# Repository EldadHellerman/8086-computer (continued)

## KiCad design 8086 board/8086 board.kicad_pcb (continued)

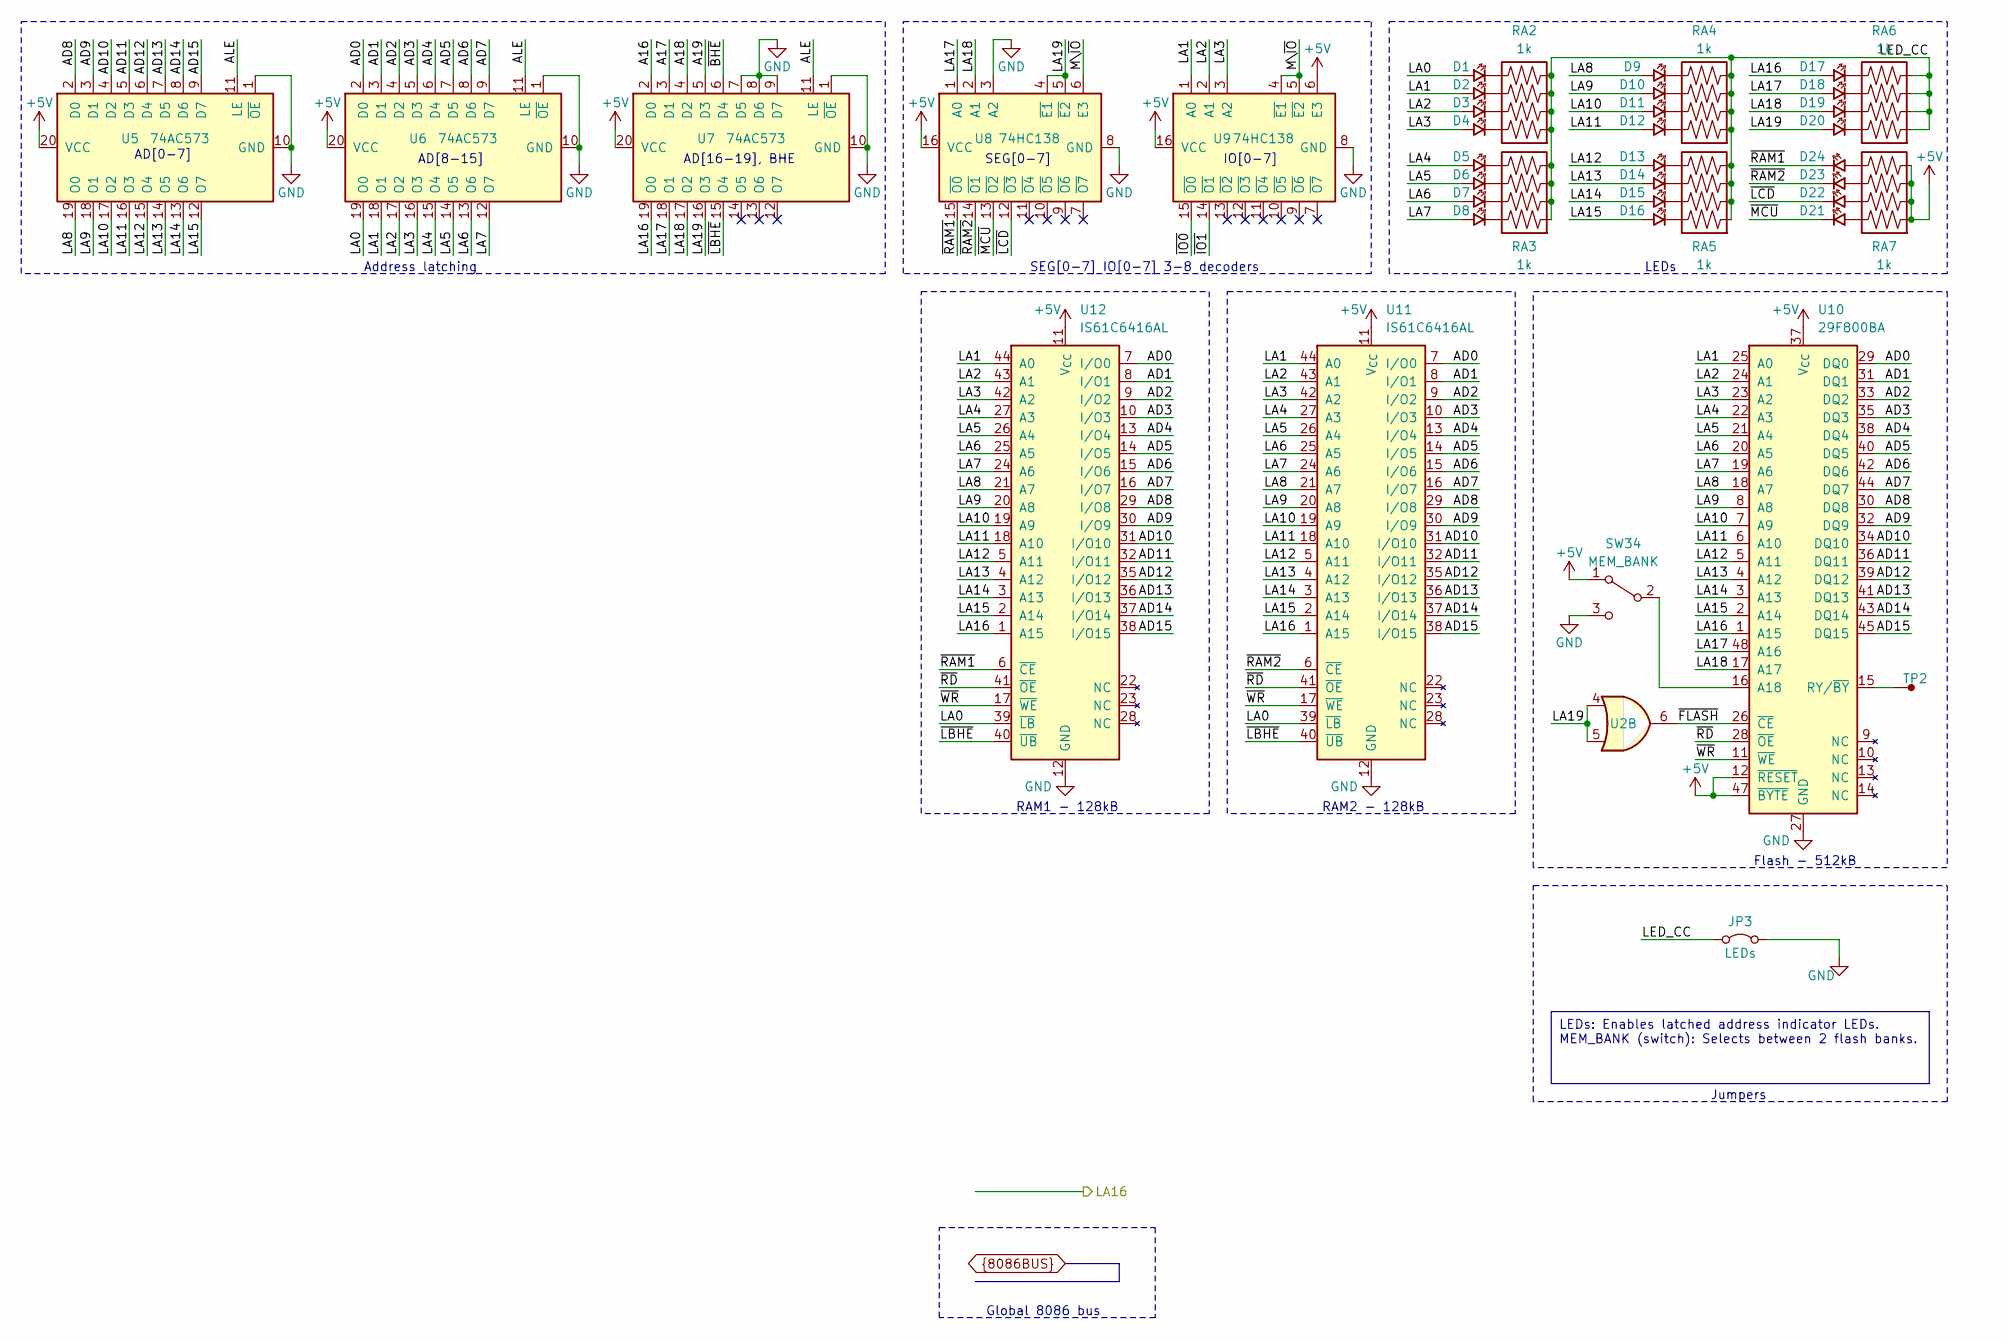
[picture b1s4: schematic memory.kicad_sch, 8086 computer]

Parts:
D1: A0; LED_0603_1608Metric_Pad1.05x0.95mm_HandSolder
D2: A1; LED_0603_1608Metric_Pad1.05x0.95mm_HandSolder
D3: A2; LED_0603_1608Metric_Pad1.05x0.95mm_HandSolder
D4: A3; LED_0603_1608Metric_Pad1.05x0.95mm_HandSolder
D5: A4; LED_0603_1608Metric_Pad1.05x0.95mm_HandSolder
D6: A5; LED_0603_1608Metric_Pad1.05x0.95mm_HandSolder
D7: A6; LED_0603_1608Metric_Pad1.05x0.95mm_HandSolder
D8: A7; LED_0603_1608Metric_Pad1.05x0.95mm_HandSolder
D9: A8; LED_0603_1608Metric_Pad1.05x0.95mm_HandSolder
D10: A9; LED_0603_1608Metric_Pad1.05x0.95mm_HandSolder
D11: A10; LED_0603_1608Metric_Pad1.05x0.95mm_HandSolder
D12: A11; LED_0603_1608Metric_Pad1.05x0.95mm_HandSolder
D13: A12; LED_0603_1608Metric_Pad1.05x0.95mm_HandSolder
D14: A13; LED_0603_1608Metric_Pad1.05x0.95mm_HandSolder
D15: A14; LED_0603_1608Metric_Pad1.05x0.95mm_HandSolder
D16: A15; LED_0603_1608Metric_Pad1.05x0.95mm_HandSolder
D17: A16; LED_0603_1608Metric_Pad1.05x0.95mm_HandSolder
D18: A17; LED_0603_1608Metric_Pad1.05x0.95mm_HandSolder
D19: A18; LED_0603_1608Metric_Pad1.05x0.95mm_HandSolder
D20: A19; LED_0603_1608Metric_Pad1.05x0.95mm_HandSolder
D21: MCU; LED_0603_1608Metric_Pad1.05x0.95mm_HandSolder
D22: LCD; LED_0603_1608Metric_Pad1.05x0.95mm_HandSolder
D23: RAM2; LED_0603_1608Metric_Pad1.05x0.95mm_HandSolder
D24: RAM1; LED_0603_1608Metric_Pad1.05x0.95mm_HandSolder
JP3: LEDs; SolderJumper-2_P1.3mm_Bridged_RoundedPad1.0x1.5mm
RA2, RA3, RA4, RA5, RA6, RA7: 1k; R_Array_Concave_4x0603
SW34: MEM_BANK; SW_SPDT_PCM12
TP2: TestPoint_Pad_1.0x1.0mm
U2: 74HC32; TSSOP-14_4.4x5mm_P0.65mm
U5, U6, U7: 74AC573; TSSOP-20_4.4x6.5mm_P0.65mm
U8, U9: 74HC138; TSSOP-16_4.4x5mm_P0.65mm
U10: 29F800BA; TSOP-I-48_18.4x12mm_P0.5mm
U11, U12: IS61C6416AL; TSOP-II-44_10.16x18.41mm_P0.8mm

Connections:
+5V: RA7.1, RA7.2, RA7.3, RA7.4, SW34.1 (A), U5.20 (VCC), U6.20 (VCC), U7.20 (VCC), U8.16 (VCC), U9.6 (E3), U9.16 (VCC), U10.12 (~RESET), U10.37 (V_{CC}), U10.47 (~BYTE), U11.11 (V_{CC}), U11.33 (V_{CC}), U12.11 (V_{CC}), U12.33 (V_{CC}); also elsewhere on the board
/IO/D/~C: D17.1 (A), U7.19 (O0), U10.1 (A15), U11.1 (A15), U12.1 (A15); also elsewhere on the board
/Memory/LA0: D1.1 (A), U6.19 (O0), U11.39 (~LB), U12.39 (~LB)
/Memory/LA1: D2.1 (A), U6.18 (O1), U9.1 (A0), U10.25 (A0), U11.44 (A0), U12.44 (A0)
/Memory/LA2: D3.1 (A), U6.17 (O2), U9.2 (A1), U10.24 (A1), U11.43 (A1), U12.43 (A1)
/Memory/LA3: D4.1 (A), U6.16 (O3), U9.3 (A2), U10.23 (A2), U11.42 (A2), U12.42 (A2)
/Memory/LA4: D5.1 (A), U6.15 (O4), U10.22 (A3), U11.27 (A3), U12.27 (A3)
/Memory/LA5: D6.1 (A), U6.14 (O5), U10.21 (A4), U11.26 (A4), U12.26 (A4)
/Memory/LA6: D7.1 (A), U6.13 (O6), U10.20 (A5), U11.25 (A5), U12.25 (A5)
/Memory/LA7: D8.1 (A), U6.12 (O7), U10.19 (A6), U11.24 (A6), U12.24 (A6)
/Memory/LA8: D9.1 (A), U5.19 (O0), U10.18 (A7), U11.21 (A7), U12.21 (A7)
/Memory/LA9: D10.1 (A), U5.18 (O1), U10.8 (A8), U11.20 (A8), U12.20 (A8)
/Memory/LA10: D11.1 (A), U5.17 (O2), U10.7 (A9), U11.19 (A9), U12.19 (A9)
/Memory/LA11: D12.1 (A), U5.16 (O3), U10.6 (A10), U11.18 (A10), U12.18 (A10)
/Memory/LA12: D13.1 (A), U5.15 (O4), U10.5 (A11), U11.5 (A11), U12.5 (A11)
/Memory/LA13: D14.1 (A), U5.14 (O5), U10.4 (A12), U11.4 (A12), U12.4 (A12)
/Memory/LA14: D15.1 (A), U5.13 (O6), U10.3 (A13), U11.3 (A13), U12.3 (A13)
/Memory/LA15: D16.1 (A), U5.12 (O7), U10.2 (A14), U11.2 (A14), U12.2 (A14)
/Memory/LA17: D18.1 (A), U7.18 (O1), U8.1 (A0), U10.48 (A16)
/Memory/LA18: D19.1 (A), U7.17 (O2), U8.2 (A1), U10.17 (A17)
/Memory/LA19: D20.1 (A), U2.4, U2.5, U7.16 (O3), U8.4 (~E1), U8.5 (~E2)
/Memory/LED_CC: JP3.1 (A), RA2.1, RA2.2, RA2.3, RA2.4, RA3.1, RA3.2, RA3.3, RA3.4, RA4.1, RA4.2, RA4.3, RA4.4, RA5.1, RA5.2, RA5.3, RA5.4, RA6.1, RA6.2, RA6.3, RA6.4
/Memory/~FLASH: U2.6, U10.26 (~CE)
/Memory/~LBHE: U7.15 (O4), U11.40 (~UB), U12.40 (~UB)
/Memory/~RAM1: D24.2 (K), U8.15 (~O0), U12.6 (~CE)
/Memory/~RAM2: D23.2 (K), U8.14 (~O1), U11.6 (~CE)
A16: U7.2 (D0); also elsewhere on the board
A17: U7.3 (D1); also elsewhere on the board
A18: U7.4 (D2); also elsewhere on the board
A19: U7.5 (D3); also elsewhere on the board
AD0: U6.2 (D0), U10.29 (DQ0), U11.7 (I/O0), U12.7 (I/O0); also elsewhere on the board
AD1: U6.3 (D1), U10.31 (DQ1), U11.8 (I/O1), U12.8 (I/O1); also elsewhere on the board
AD2: U6.4 (D2), U10.33 (DQ2), U11.9 (I/O2), U12.9 (I/O2); also elsewhere on the board
AD3: U6.5 (D3), U10.35 (DQ3), U11.10 (I/O3), U12.10 (I/O3); also elsewhere on the board
AD4: U6.6 (D4), U10.38 (DQ4), U11.13 (I/O4), U12.13 (I/O4); also elsewhere on the board
AD5: U6.7 (D5), U10.40 (DQ5), U11.14 (I/O5), U12.14 (I/O5); also elsewhere on the board
AD6: U6.8 (D6), U10.42 (DQ6), U11.15 (I/O6), U12.15 (I/O6); also elsewhere on the board
AD7: U6.9 (D7), U10.44 (DQ7), U11.16 (I/O7), U12.16 (I/O7); also elsewhere on the board
AD8: U5.2 (D0), U10.30 (DQ8), U11.29 (I/O8), U12.29 (I/O8); also elsewhere on the board
AD9: U5.3 (D1), U10.32 (DQ9), U11.30 (I/O9), U12.30 (I/O9); also elsewhere on the board
AD10: U5.4 (D2), U10.34 (DQ10), U11.31 (I/O10), U12.31 (I/O10); also elsewhere on the board
AD11: U5.5 (D3), U10.36 (DQ11), U11.32 (I/O11), U12.32 (I/O11); also elsewhere on the board
AD12: U5.6 (D4), U10.39 (DQ12), U11.35 (I/O12), U12.35 (I/O12); also elsewhere on the board
AD13: U5.7 (D5), U10.41 (DQ13), U11.36 (I/O13), U12.36 (I/O13); also elsewhere on the board
AD14: U5.8 (D6), U10.43 (DQ14), U11.37 (I/O14), U12.37 (I/O14); also elsewhere on the board
AD15: U5.9 (D7), U10.45 (DQ15), U11.38 (I/O15), U12.38 (I/O15); also elsewhere on the board
ALE: U5.11 (LE), U6.11 (LE), U7.11 (LE); also elsewhere on the board
GND: JP3.2 (B), SW34.3 (C), U5.1 (~OE), U5.10 (GND), U6.1 (~OE), U6.10 (GND), U7.1 (~OE), U7.7 (D5), U7.8 (D6), U7.9 (D7), U7.10 (GND), U8.3 (A2), U8.8 (GND), U9.8 (GND), U10.27 (GND), U10.46 (GND), U11.12 (GND), U11.34 (GND), U12.12 (GND), U12.34 (GND); also elsewhere on the board
M\~IO: U8.6 (E3), U9.4 (~E1), U9.5 (~E2); also elsewhere on the board
unnamed: D1.2 (K), RA2.5
unnamed: D2.2 (K), RA2.6
unnamed: D3.2 (K), RA2.7
unnamed: D4.2 (K), RA2.8
unnamed: D5.2 (K), RA3.5
unnamed: D6.2 (K), RA3.6
unnamed: D7.2 (K), RA3.7
unnamed: D8.2 (K), RA3.8
unnamed: D9.2 (K), RA4.5
unnamed: D10.2 (K), RA4.6
unnamed: D11.2 (K), RA4.7
unnamed: D12.2 (K), RA4.8
unnamed: D13.2 (K), RA5.5
unnamed: D14.2 (K), RA5.6
unnamed: D15.2 (K), RA5.7
unnamed: D16.2 (K), RA5.8
unnamed: D17.2 (K), RA6.5
unnamed: D18.2 (K), RA6.6
unnamed: D19.2 (K), RA6.7
unnamed: D20.2 (K), RA6.8
unnamed: D21.1 (A), RA7.8
unnamed: D22.1 (A), RA7.7
unnamed: D23.1 (A), RA7.6
unnamed: D24.1 (A), RA7.5
unnamed: SW34.2 (B), U10.16 (A18)
unnamed: TP2.1, U10.15 (RY/~BY)
~BHE: U7.6 (D4); also elsewhere on the board
~IO0: U9.15 (~O0); also elsewhere on the board
~IO1: U9.14 (~O1); also elsewhere on the board
~LCD: D22.2 (K), U8.12 (~O3); also elsewhere on the board
~MCU: D21.2 (K), U8.13 (~O2); also elsewhere on the board
~RD: U10.28 (~OE), U11.41 (~OE), U12.41 (~OE); also elsewhere on the board
~WR: U10.11 (~WE), U11.17 (~WE), U12.17 (~WE); also elsewhere on the board

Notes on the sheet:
LEDs: Enables latched address indicator LEDs. MEM_BANK (switch): Selects between 2 flash banks.
IO[0-7]
AD[16-19], BHE
SEG[0-7] IO[0-7] 3-8 decoders
RAM1 - 128kB
Address latching
AD[0-7]
LEDs
AD[8-15]
SEG[0-7]
Jumpers
RAM2 - 128kB
Flash - 512kB
Global 8086 bus

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
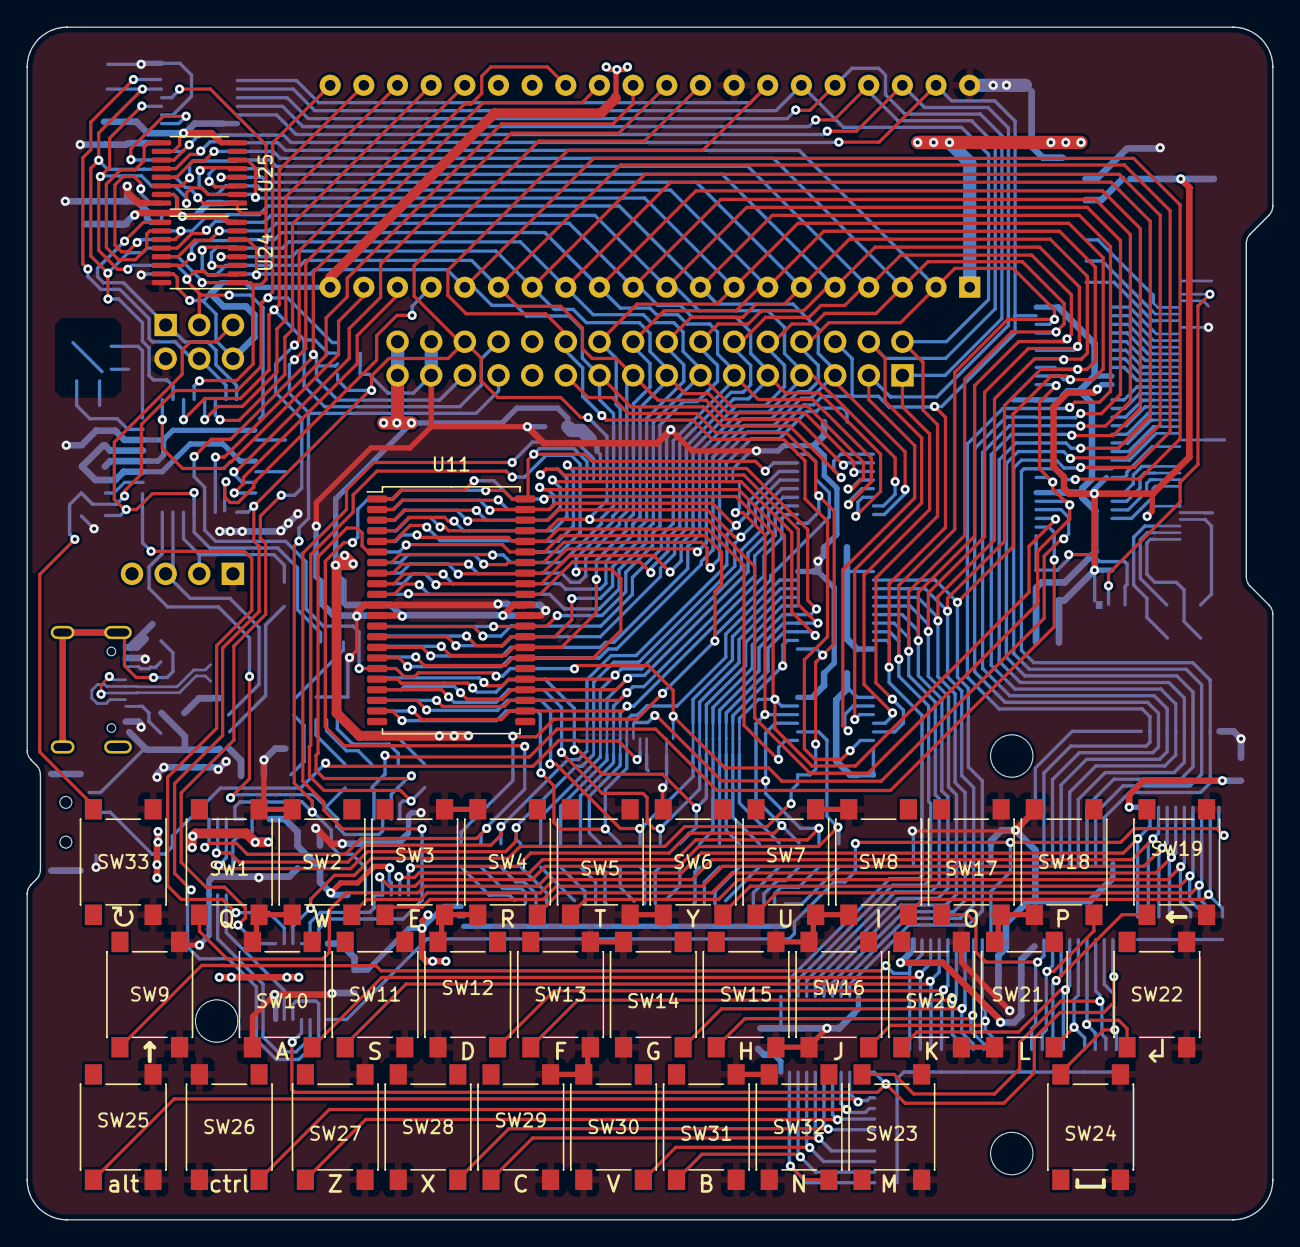
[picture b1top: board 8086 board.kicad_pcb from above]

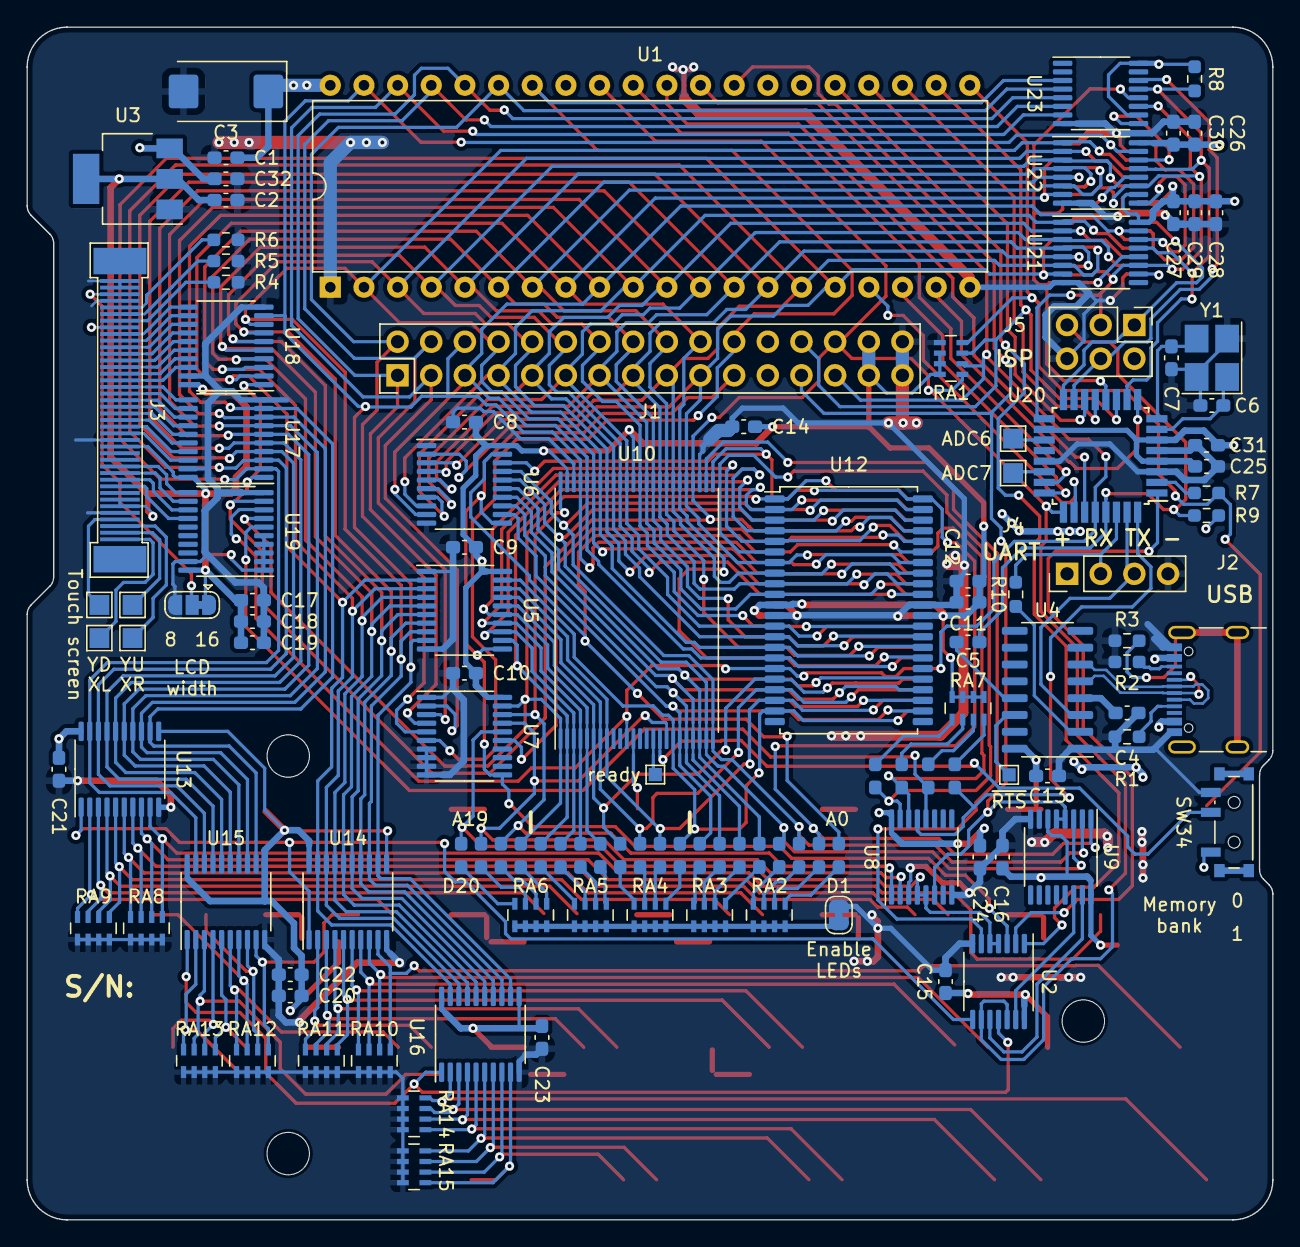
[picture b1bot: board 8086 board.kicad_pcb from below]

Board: 2 copper layers, 94.0 x 90.0 mm, 159 parts (123 on the bottom side), 181 nets.

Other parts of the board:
C4: 1uF; C_0603_1608Metric_Pad1.08x0.95mm_HandSolder
TP3: XL; TestPoint_Pad_1.5x1.5mm
TP4: YU; TestPoint_Pad_1.5x1.5mm
TP5: XR; TestPoint_Pad_1.5x1.5mm
TP6: YD; TestPoint_Pad_1.5x1.5mm
TP7: ADC6; TestPoint_Pad_1.5x1.5mm
TP8: ADC7; TestPoint_Pad_1.5x1.5mm
U4: CH340C; SOIC-16_3.9x9.9mm_P1.27mm

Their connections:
+5V: U4.16 (VCC); also elsewhere on the board
/Microcontroller/DN: U4.6 (UD-); also elsewhere on the board
/Microcontroller/DP: U4.5 (UD+); also elsewhere on the board
/Microcontroller/RX: U4.3 (RXD); also elsewhere on the board
GND: C4.1, U4.1 (GND); also elsewhere on the board
unnamed 155: U4.2 (TXD); also elsewhere on the board
unnamed: C4.2, U4.4 (V3)
unnamed 157: U4.13 (~DTR); also elsewhere on the board

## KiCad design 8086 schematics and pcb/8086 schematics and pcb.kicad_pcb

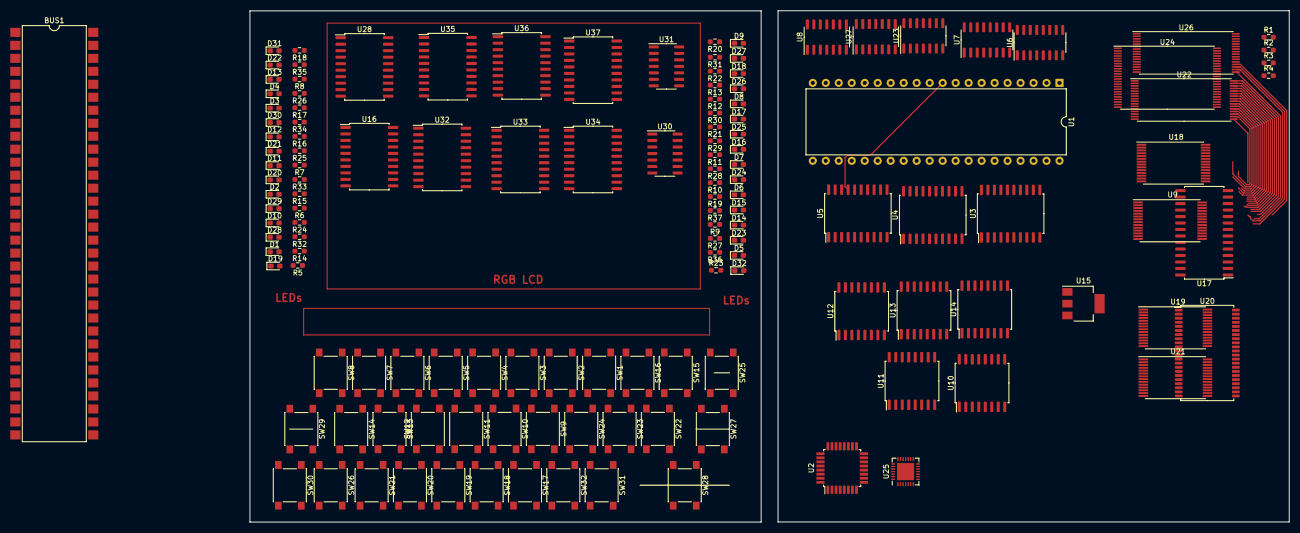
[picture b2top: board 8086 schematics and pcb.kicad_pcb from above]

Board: 2 copper layers, 203.3 x 100.0 mm, 138 parts (0 on the bottom side), 198 nets.

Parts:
BUS1: 8086 BUS; SMDIP-64_W15.24mm
D1, D2, D3, D4, D5, D6, D7, D8, D9, D10, D11, D12, D13, D14, D15, D16, D17, D18, D19, D20, D21, D22, D23, D24, D25, D26, D27, D28, D29, D30, D31, D32: LED_Filled; LED_0603_1608Metric_Pad1.05x0.95mm_HandSolder
R1, R2, R3, R4: 10K; R_0603_1608Metric_Pad0.98x0.95mm_HandSolder
R5, R6, R7, R8, R9, R10, R11, R12, R13, R14, R15, R16, R17, R18, R19, R20, R21, R22, R23, R24, R25, R26, R27, R28, R29, R30, R31, R32, R33, R34, R35, R36, R37: R_US; R_0603_1608Metric_Pad0.98x0.95mm_HandSolder
SW1, SW2, SW3, SW4, SW5, SW6, SW7, SW8, SW9, SW10, SW11, SW12, SW13, SW14, SW15, SW16, SW17, SW18, SW19, SW20, SW21, SW22, SW23, SW24, SW25, SW26, SW27, SW28, SW29, SW30, SW31, SW32: SW_Push; SW_Push_1P1T_NO_6x6mm_H9.5mm
U1: P8086-2; DIP-40_W15.24mm
U2: ATmega328P-A; TQFP-32_7x7mm_P0.8mm
U3, U4, U5: 74HC373; SOIC-20W_7.5x12.8mm_P1.27mm
U6, U7: 74LS138; SOIC-16_3.9x9.9mm_P1.27mm
U8, U30: 74AC00; SOIC-14_3.9x8.7mm_P1.27mm
U9, U18, U19, U21: IS61C256AH; TSOP-I-28_11.8x8mm_P0.55mm
U10, U11, U12: 74HC595; SOIC-16W_7.5x10.3mm_P1.27mm
U13, U14: 74HC165; SOIC-16W_7.5x10.3mm_P1.27mm
U15: AMS1117-3.3; SOT-223-3_TabPin2
U16, U28, U32, U33, U34, U35, U36, U37: 74AC373; SOIC-20W_7.5x12.8mm_P1.27mm
U17: CXK58257AM; SOIC-28W_7.5x17.9mm_P1.27mm
U20: IS61C3216; TSOP-II-44_10.16x18.41mm_P0.8mm
U22, U26: AM29F002; TSOP-I-32_18.4x8mm_P0.5mm
U23: 74HC14; SOIC-14_3.9x8.7mm_P1.27mm
U24: 28F400; TSOP-I-48_18.4x12mm_P0.5mm
U25: CP2102N-Axx-xQFN28; QFN-28-1EP_5x5mm_P0.5mm_EP3.35x3.35mm
U27, U31: 74HC02; SOIC-14_3.9x8.7mm_P1.27mm

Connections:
+3.3V: BUS1.43 (3V3), BUS1.44 (3V3), U15.2 (VO)
+5V: BUS1.41 (5V), BUS1.42 (5V), R1.1, R2.1, R3.1, R4.1, SW1.1, SW2.1, SW3.1, SW4.1, SW5.1, SW6.1, SW7.1, SW8.1, SW9.1, SW10.1, SW11.1, SW12.1, SW13.1, SW14.1, SW15.1, SW16.1, SW17.1, SW18.1, SW19.1, SW20.1, SW21.1, SW22.1, SW23.1, SW24.1, SW25.1, SW26.1, SW27.1, SW28.1, SW29.1, SW30.1, SW31.1, SW32.1, U1.33 (NM/~MX), U1.40 (V_{CC}), U2.4 (VCC), U2.6 (VCC), U2.18 (AVCC), U3.20 (VCC), U4.20 (VCC), U5.20 (VCC), U6.6 (E3), U6.16 (VCC), U7.16 (VCC), U8.14 (V_{CC}), U9.28 (V_{CC}), U10.16 (VCC), U11.16 (VCC), U12.16 (VCC), U13.16 (V_{CC}), U14.16 (V_{CC}), U15.3 (VI), U16.20 (VCC), U17.28 (V_{CC}), U18.28 (V_{CC}), U19.28 (V_{CC}), U20.11 (V_{CC}), U20.33 (V_{CC}), U21.28 (V_{CC}), U22.8 (V_{CC}), U22.9 (~RESET), U23.14 (V_{CC}), U24.12 (~RP), U24.13 (V_{PP}), U24.14 (~WP), U24.37 (V_{CC}), U24.47 (~BYTE), U26.8 (V_{CC}), U26.9 (~RESET), U27.14 (V_{CC}), U28.20 (VCC), U30.14 (V_{CC}), U31.14 (V_{CC}), U32.20 (VCC), U33.20 (VCC), U34.20 (VCC), U35.20 (VCC), U36.20 (VCC), U37.20 (VCC)
/8086 Module - 1/ALE: U3.11 (LE), U4.11 (LE), U5.11 (LE), U23.12
/8086 Module - 1/CPUALE: U1.25 (ALE), U27.2
/8086 Module - 1/LA0: U5.2 (O0), U20.39 (~LB), U23.1
/8086 Module - 1/LA1: U5.5 (O1), U6.1 (A0), U9.10 (A0), U17.10 (A0), U18.10 (A0), U19.10 (A0), U20.44 (A0), U21.10 (A0), U22.20 (A0), U24.25 (A0), U26.20 (A0)
/8086 Module - 1/LA2: U5.6 (O2), U6.2 (A1), U9.9 (A1), U17.9 (A1), U18.9 (A1), U19.9 (A1), U20.43 (A1), U21.9 (A1), U22.19 (A1), U24.24 (A1), U26.19 (A1)
/8086 Module - 1/LA3: U5.9 (O3), U6.3 (A2), U9.8 (A2), U17.8 (A2), U18.8 (A2), U19.8 (A2), U20.42 (A2), U21.8 (A2), U22.18 (A2), U24.23 (A2), U26.18 (A2)
/8086 Module - 1/LA4: U5.12 (O4), U9.7 (A3), U17.7 (A3), U18.7 (A3), U19.7 (A3), U20.27 (A3), U21.7 (A3), U22.17 (A3), U24.22 (A3), U26.17 (A3)
/8086 Module - 1/LA5: U5.15 (O5), U9.6 (A4), U17.6 (A4), U18.6 (A4), U19.6 (A4), U20.26 (A4), U21.6 (A4), U22.16 (A4), U24.21 (A4), U26.16 (A4)
/8086 Module - 1/LA6: U5.16 (O6), U9.5 (A5), U17.5 (A5), U18.5 (A5), U19.5 (A5), U20.25 (A5), U21.5 (A5), U22.15 (A5), U24.20 (A5), U26.15 (A5)
/8086 Module - 1/LA7: U5.19 (O7), U9.4 (A6), U17.4 (A6), U18.4 (A6), U19.4 (A6), U20.24 (A6), U21.4 (A6), U22.14 (A6), U24.19 (A6), U26.14 (A6)
/8086 Module - 1/LA8: U3.2 (O0), U9.3 (A7), U17.3 (A7), U18.3 (A7), U19.3 (A7), U20.21 (A7), U21.3 (A7), U22.13 (A7), U24.18 (A7), U26.13 (A7)
/8086 Module - 1/LA9: U3.5 (O1), U9.25 (A8), U17.25 (A8), U18.25 (A8), U19.25 (A8), U20.20 (A8), U21.25 (A8), U22.3 (A8), U24.8 (A8), U26.3 (A8)
/8086 Module - 1/LA10: U3.6 (O2), U9.24 (A9), U17.24 (A9), U18.24 (A9), U19.24 (A9), U20.19 (A9), U21.24 (A9), U22.2 (A9), U24.7 (A9), U26.2 (A9)
/8086 Module - 1/LA11: U3.9 (O3), U9.21 (A10), U17.21 (A10), U18.21 (A10), U19.21 (A10), U20.18 (A10), U21.21 (A10), U22.31 (A10), U24.6 (A10), U26.31 (A10)
/8086 Module - 1/LA12: U3.12 (O4), U9.23 (A11), U17.23 (A11), U18.23 (A11), U19.23 (A11), U20.5 (A11), U21.23 (A11), U22.1 (A11), U24.5 (A11), U26.1 (A11)
/8086 Module - 1/LA13: U3.15 (O5), U9.2 (A12), U17.2 (A12), U18.2 (A12), U19.2 (A12), U20.4 (A12), U21.2 (A12), U22.12 (A12), U24.4 (A12), U26.12 (A12)
/8086 Module - 1/LA14: U3.16 (O6), U9.26 (A13), U17.26 (A13), U18.26 (A13), U19.26 (A13), U20.3 (A13), U21.26 (A13), U22.4 (A13), U24.3 (A13), U26.4 (A13)
/8086 Module - 1/LA15: U3.19 (O7), U9.1 (A14), U17.1 (A14), U18.1 (A14), U19.1 (A14), U20.2 (A14), U21.1 (A14), U22.5 (A14), U24.2 (A14), U26.5 (A14)
/8086 Module - 1/LA16: U4.2 (O0), U7.1 (A0), U22.11 (A15), U24.1 (A15), U26.11 (A15)
/8086 Module - 1/LA17: U4.5 (O1), U7.2 (A1), U22.10 (A16), U24.48 (A16), U26.10 (A16)
/8086 Module - 1/LA18: U4.6 (O2), U7.3 (A2), U22.6 (A17), U24.17 (A17), U26.6 (A17)
/8086 Module - 1/LA19: U4.9 (O3), U7.4 (~E1), U7.5 (~E2), U23.3
/8086 Module - 1/LBHE: U8.5, U8.13, U23.10
/8086 Module - 1/M/~IO: U1.28 (M/~IO), U6.4 (~E1), U6.5 (~E2), U7.6 (E3)
/8086 Module - 1/SEG0: U8.2, U8.4, U23.8
/8086 Module - 1/~LA0: U8.1, U8.9, U23.2
/8086 Module - 1/~LA19: U23.4, U24.26 (~CE)
/8086 Module - 1/~LBHE: U4.12 (O4), U20.40 (~UB), U23.11
/8086 Module - 1/~SEG0: U7.15 (~O0), U23.9
/8086 Module - 1/~SEG1: U7.14 (~O1), U20.6 (~CE), U23.5
/8086 Module - 2/~MEM1H: U8.11, U21.20 (~CE), U26.30 (~CE)
/8086 Module - 2/~MEM1L: U8.8, U19.20 (~CE), U22.30 (~CE)
/8086 Module - 2/~SEG0H: U8.6, U18.20 (~CE)
/8086 Module - 2/~SEG0L: U8.3, U9.20 (~CE), U17.20 (~CE)
/8086 Module - 2/~WRP: U22.7 (~WE), U24.11 (~WE), U26.7 (~WE)
/IO Module/WR0: U28.11 (LE), U31.10, U35.11 (LE)
/IO Module/WR1: U31.13, U36.11 (LE), U37.11 (LE)
/IO Module/~RD0: U16.1 (~OE), U30.3, U32.1 (~OE)
/IO Module/~RD1: U30.6, U33.1 (~OE), U34.1 (~OE)
/Microcontroller Module/REG_OE: U2.23 (PC0), U10.13 (~OE), U11.13 (~OE), U12.13 (~OE)
/Microcontroller Module/REG_RCLK: U2.14 (PB2), U10.12 (RCLK), U11.12 (RCLK), U12.12 (RCLK)
/Microcontroller Module/REG_SHLD: U2.24 (PC1), U13.1 (SH/~LD), U14.1 (SH/~LD)
/Microcontroller Module/SPI_MISO: U2.16 (PB4), U14.9 (QH)
/Microcontroller Module/SPI_MOSI: U2.15 (PB3), U10.14 (SER)
/Microcontroller Module/SPI_SCK: U2.17 (PB5), U10.11 (SRCLK), U11.11 (SRCLK), U12.11 (SRCLK)
A16: BUS1.17 (A16), U1.38 (A16), U4.3 (D0), U12.15 (QA)
A17: BUS1.18 (A17), U1.37 (A17), U4.4 (D1), U12.1 (QB)
A18: BUS1.19 (A18), U1.36 (A18), U4.7 (D2), U12.2 (QC)
A19: BUS1.20 (A19), U1.35 (A19), U4.8 (D3), U12.3 (QD)
AD0: BUS1.1 (AD0), U1.16 (AD0), U5.3 (D0), U9.11 (I/O0), U10.15 (QA), U13.11 (A), U16.2 (O0), U17.11 (I/O0), U19.11 (I/O0), U20.7 (I/O0), U22.21 (DQ0), U24.29 (DQ0), U28.3 (D0), U33.2 (O0), U36.3 (D0)
AD1: BUS1.2 (AD1), BUS1.3 (AD2), U1.15 (AD1), U5.4 (D1), U9.12 (I/O1), U10.1 (QB), U13.12 (B), U16.5 (O1), U17.12 (I/O1), U19.12 (I/O1), U20.8 (I/O1), U22.22 (DQ1), U24.31 (DQ1), U28.4 (D1), U33.5 (O1), U36.4 (D1)
AD2: U1.14 (AD2), U5.7 (D2), U9.13 (I/O2), U10.2 (QC), U13.13 (C), U16.6 (O2), U17.13 (I/O2), U19.13 (I/O2), U20.9 (I/O2), U22.23 (DQ2), U24.33 (DQ2), U28.7 (D2), U33.6 (O2), U36.7 (D2)
AD3: BUS1.4 (AD3), U1.13 (AD3), U5.8 (D3), U9.15 (I/O3), U10.3 (QD), U13.14 (D), U16.9 (O3), U17.15 (I/O3), U19.15 (I/O3), U20.10 (I/O3), U22.25 (DQ3), U24.35 (DQ3), U28.8 (D3), U33.9 (O3), U36.8 (D3)
AD4: BUS1.5 (AD4), U1.12 (AD4), U5.13 (D4), U9.16 (I/O4), U10.4 (QE), U13.3 (E), U16.12 (O4), U17.16 (I/O4), U19.16 (I/O4), U20.13 (I/O4), U22.26 (DQ4), U24.38 (DQ4), U28.13 (D4), U33.12 (O4), U36.13 (D4)
AD5: BUS1.6 (AD5), U1.11 (AD5), U5.14 (D5), U9.17 (I/O5), U10.5 (QF), U13.4 (F), U16.15 (O5), U17.17 (I/O5), U19.17 (I/O5), U20.14 (I/O5), U22.27 (DQ5), U24.40 (DQ5), U28.14 (D5), U33.15 (O5), U36.14 (D5)
AD6: BUS1.7 (AD6), U1.10 (AD6), U5.17 (D6), U9.18 (I/O6), U10.6 (QG), U13.5 (G), U16.16 (O6), U17.18 (I/O6), U19.18 (I/O6), U20.15 (I/O6), U22.28 (DQ6), U24.42 (DQ6), U28.17 (D6), U33.16 (O6), U36.17 (D6)
AD7: BUS1.8 (AD7), U1.9 (AD7), U5.18 (D7), U9.19 (I/O7), U10.7 (QH), U13.6 (H), U16.19 (O7), U17.19 (I/O7), U19.19 (I/O7), U20.16 (I/O7), U22.29 (DQ7), U24.44 (DQ7), U28.18 (D7), U33.19 (O7), U36.18 (D7)
AD8: BUS1.9 (AD8), U1.8 (AD8), U3.3 (D0), U11.15 (QA), U14.11 (A), U18.11 (I/O0), U20.29 (I/O8), U21.11 (I/O0), U24.30 (DQ8), U26.21 (DQ0), U32.2 (O0), U34.2 (O0), U35.3 (D0), U37.3 (D0)
AD9: BUS1.10 (AD9), U1.7 (AD9), U3.4 (D1), U11.1 (QB), U14.12 (B), U18.12 (I/O1), U20.30 (I/O9), U21.12 (I/O1), U24.32 (DQ9), U26.22 (DQ1), U32.5 (O1), U34.5 (O1), U35.4 (D1), U37.4 (D1)
AD10: BUS1.11 (AD10), U1.6 (AD10), U3.7 (D2), U11.2 (QC), U14.13 (C), U18.13 (I/O2), U20.31 (I/O10), U21.13 (I/O2), U24.34 (DQ10), U26.23 (DQ2), U32.6 (O2), U34.6 (O2), U35.7 (D2), U37.7 (D2)
AD11: BUS1.12 (AD11), U1.5 (AD11), U3.8 (D3), U11.3 (QD), U14.14 (D), U18.15 (I/O3), U20.32 (I/O11), U21.15 (I/O3), U24.36 (DQ11), U26.25 (DQ3), U32.9 (O3), U34.9 (O3), U35.8 (D3), U37.8 (D3)
AD12: BUS1.13 (AD12), U1.4 (AD12), U3.13 (D4), U11.4 (QE), U14.3 (E), U18.16 (I/O4), U20.35 (I/O12), U21.16 (I/O4), U24.39 (DQ12), U26.26 (DQ4), U32.12 (O4), U34.12 (O4), U35.13 (D4), U37.13 (D4)
AD13: BUS1.14 (AD13), U1.3 (AD13), U3.14 (D5), U11.5 (QF), U14.4 (F), U18.17 (I/O5), U20.36 (I/O13), U21.17 (I/O5), U24.41 (DQ13), U26.27 (DQ5), U32.15 (O5), U34.15 (O5), U35.14 (D5), U37.14 (D5)
AD14: BUS1.15 (AD14), U1.2 (AD14), U3.17 (D6), U11.6 (QG), U14.5 (G), U18.18 (I/O6), U20.37 (I/O14), U21.18 (I/O6), U24.43 (DQ14), U26.28 (DQ6), U32.16 (O6), U34.16 (O6), U35.17 (D6), U37.17 (D6)
AD15: BUS1.16 (AD15), U1.39 (AD15), U3.18 (D7), U11.7 (QH), U14.6 (H), U18.19 (I/O7), U20.38 (I/O15), U21.19 (I/O7), U24.45 (DQ15), U26.29 (DQ7), U32.19 (O7), U34.19 (O7), U35.18 (D7), U37.18 (D7)
BUSALE: BUS1.22 (ALE), U2.2 (PD4), U27.3
CLK: BUS1.40 (CLK), U1.19 (CLK), U2.9 (PD5)
GND: BUS1.47 (GND), BUS1.48 (GND), R5.2, R6.2, R7.2, R8.2, R9.2, R10.2, R11.2, R12.2, R13.2, R14.2, R15.2, R16.2, R17.2, R18.2, R19.2, R20.2, R21.2, R22.2, R23.2, R24.2, R25.2, R26.2, R27.2, R28.2, R29.2, R30.2, R31.2, R32.2, R33.2, R34.2, R35.2, R36.2, R37.2, U1.1 (GND), U1.20 (GND), U2.3 (GND), U2.5 (GND), U2.21 (GND), U3.1 (~OE), U3.10 (GND), U4.1 (~OE), U4.10 (GND), U5.1 (~OE), U5.10 (GND), U6.8 (GND), U7.8 (GND), U8.7 (GND), U9.14 (GND), U10.8 (GND), U10.10 (~SRCLR), U11.8 (GND), U11.10 (~SRCLR), U12.8 (GND), U12.10 (~SRCLR), U13.8 (GND), U14.8 (GND), U15.1 (GND), U16.10 (GND), U17.14 (GND), U18.14 (GND), U19.14 (GND), U20.12 (GND), U20.34 (GND), U21.14 (GND), U22.24 (GND), U23.7 (GND), U24.27 (GND), U24.46 (GND), U26.24 (GND), U27.7 (GND), U28.1 (~OE), U28.10 (GND), U30.7 (GND), U31.7 (GND), U32.10 (GND), U33.10 (GND), U34.10 (GND), U35.1 (~OE), U35.10 (GND), U36.1 (~OE), U36.10 (GND), U37.1 (~OE), U37.10 (GND)
HLDA: BUS1.38 (HLDA), U1.30 (HLDA), U2.13 (PB1)
HOLD: BUS1.37 (HOLD), U1.31 (HOLD), U2.12 (PB0)
INTR: BUS1.35 (INTR), U1.18 (INTR), U2.25 (PC2)
NMI: BUS1.34 (NMI), U1.17 (NMI), U2.26 (PC3)
unnamed: D1.2 (A), U28.5 (O1)
unnamed: D1.1 (K), R11.1
unnamed: D2.2 (A), U28.6 (O2)
unnamed: D2.1 (K), R10.1
unnamed: D3.2 (A), U28.2 (O0)
unnamed: D3.1 (K), R12.1
unnamed: D4.2 (A), U28.9 (O3)
unnamed: D4.1 (K), R5.1
unnamed: D5.2 (A), U28.12 (O4)
unnamed: D5.1 (K), R6.1
unnamed: D6.2 (A), U28.15 (O5)
unnamed: D6.1 (K), R7.1
unnamed: D7.2 (A), U28.16 (O6)
unnamed: D7.1 (K), R8.1
unnamed: D8.2 (A), U28.19 (O7)
unnamed: D8.1 (K), R9.1
unnamed: D9.2 (A), U35.2 (O0)
unnamed: D9.1 (K), R13.1
unnamed: D10.2 (A), U35.12 (O4)
unnamed: D10.1 (K), R17.1
unnamed: D11.2 (A), U35.5 (O1)
unnamed: D11.1 (K), R14.1
unnamed: D12.2 (A), U35.15 (O5)
unnamed: D12.1 (K), R18.1
unnamed: D13.2 (A), U35.6 (O2)
unnamed: D13.1 (K), R15.1
unnamed: D14.2 (A), U35.16 (O6)
unnamed: D14.1 (K), R19.1
unnamed: D15.2 (A), U35.9 (O3)
unnamed: D15.1 (K), R16.1
unnamed: D16.2 (A), U35.19 (O7)
unnamed: D16.1 (K), R20.1
unnamed: D17.2 (A), U36.2 (O0)
unnamed: D17.1 (K), R21.1
unnamed: D18.2 (A), U36.12 (O4)
unnamed: D18.1 (K), R25.1
unnamed: D19.2 (A), U36.5 (O1)
unnamed: D19.1 (K), R22.1
unnamed: D20.2 (A), U36.15 (O5)
unnamed: D20.1 (K), R26.1
unnamed: D21.2 (A), U36.6 (O2)
unnamed: D21.1 (K), R23.1
unnamed: D22.2 (A), U36.16 (O6)
unnamed: D22.1 (K), R27.1
unnamed: D23.2 (A), U36.9 (O3)
unnamed: D23.1 (K), R24.1
unnamed: D24.2 (A), U36.19 (O7)
unnamed: D24.1 (K), R28.1
unnamed: D25.2 (A), U37.2 (O0)
unnamed: D25.1 (K), R29.1
unnamed: D26.2 (A), U37.12 (O4)
unnamed: D26.1 (K), R33.1
unnamed: D27.2 (A), U37.5 (O1)
unnamed: D27.1 (K), R30.1
unnamed: D28.2 (A), U37.15 (O5)
unnamed: D28.1 (K), R34.1
unnamed: D29.2 (A), U37.6 (O2)
unnamed: D29.1 (K), R31.1
unnamed: D30.2 (A), U37.16 (O6)
unnamed: D30.1 (K), R35.1
unnamed: D31.2 (A), U37.9 (O3)
unnamed: D31.1 (K), R32.1
unnamed: D32.2 (A), U37.19 (O7)
unnamed: D32.1 (K), R36.1
unnamed: U8.10, U8.12
unnamed: U16.11 (LE), U32.11 (LE), U33.11 (LE), U34.11 (LE)
unnamed: U10.9 (QH'), U11.14 (SER)
unnamed: U11.9 (QH'), U12.14 (SER)
unnamed: SW1.2, U16.3 (D0)
unnamed: SW2.2, U16.4 (D1)
unnamed: SW3.2, U16.7 (D2)
unnamed: SW4.2, U16.8 (D3)
unnamed: SW5.2, U16.13 (D4)
unnamed: SW6.2, U16.14 (D5)
unnamed: SW7.2, U16.17 (D6)
unnamed: R37.1, SW8.2, U16.18 (D7)
unnamed: U23.13, U27.1
unnamed: U30.1, U30.2, U31.1
unnamed: U30.4, U30.5, U31.4
unnamed: SW9.2, U32.3 (D0)
unnamed: SW10.2, U32.4 (D1)
unnamed: SW11.2, U32.7 (D2)
unnamed: SW12.2, U32.8 (D3)
unnamed: SW13.2, U32.13 (D4)
unnamed: SW14.2, U32.14 (D5)
unnamed: SW15.2, U32.17 (D6)
unnamed: SW16.2, U32.18 (D7)
unnamed: SW17.2, U33.3 (D0)
unnamed: SW18.2, U33.4 (D1)
unnamed: SW19.2, U33.7 (D2)
unnamed: SW20.2, U33.8 (D3)
unnamed: SW21.2, U33.13 (D4)
unnamed: SW22.2, U33.14 (D5)
unnamed: SW23.2, U33.17 (D6)
unnamed: SW24.2, U33.18 (D7)
unnamed: SW25.2, U34.3 (D0)
unnamed: SW26.2, U34.4 (D1)
unnamed: SW27.2, U34.7 (D2)
unnamed: SW28.2, U34.8 (D3)
unnamed: SW29.2, U34.13 (D4)
unnamed: SW30.2, U34.14 (D5)
unnamed: SW31.2, U34.17 (D6)
unnamed: SW32.2, U34.18 (D7)
READY: BUS1.25 (READY), R4.2, U1.22 (READY), U2.28 (PC5)
RESET: BUS1.39 (RESET), R3.2, U1.21 (RESET), U2.10 (PD6)
~BHE: BUS1.21 (~BHE), U1.34 (~BHE), U4.13 (D4)
~INTA: BUS1.36 (~INTA), U1.24 (~INTA), U2.11 (PD7)
~IO0: BUS1.26 (~IO0), U6.15 (~O0), U31.3, U31.9
~IO1: BUS1.27 (~IO1), U6.14 (~O1), U31.6, U31.12
~IO2: BUS1.28 (~IO2), U6.13 (~O2)
~IO3: BUS1.29 (~IO3), U6.12 (~O3)
~IO4: BUS1.49 (~IO4), U6.11 (~O4)
~IO5: BUS1.50 (~IO5), U6.10 (~O5)
~IO6: BUS1.51 (~IO6), U6.9 (~O6)
~IO7: BUS1.52 (~IO7), U6.7 (~O7)
~RD: BUS1.23 (~RD), R1.2, U1.32 (~RD), U2.32 (PD2), U9.22 (~OE), U17.22 (~OE), U18.27 (~WE), U19.22 (~OE), U20.41 (~OE), U21.22 (~OE), U22.32 (~OE), U24.28 (~OE), U26.32 (~OE), U31.2, U31.5
~SEG2: BUS1.53 (~SEG2), U7.13 (~O2)
~SEG3: BUS1.54 (~SEG3), U7.12 (~O3)
~SEG4: BUS1.55 (~SEG4), U7.11 (~O4)
~SEG5: BUS1.30 (~SEG5), U7.10 (~O5)
~SEG6: BUS1.31 (~SEG6), U7.9 (~O6)
~SEG7: BUS1.32 (~SEG7), U7.7 (~O7)
~TEST: BUS1.33 (~TEST), U1.23 (~TEST), U2.27 (PC4)
~WR: BUS1.24 (~WR), R2.2, U1.29 (~WR), U2.1 (PD3), U9.27 (~WE), U17.27 (~WE), U18.22 (~OE), U19.27 (~WE), U20.17 (~WE), U21.27 (~WE), U31.8, U31.11

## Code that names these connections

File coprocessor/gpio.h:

#ifndef GPIO_H_
#define GPIO_H_

/**
 * @brief Hardware defenition for which pin is what, as well as preprocessor directives for easy GPIO control.
 * 
 * This file maps all signals to their respective ports and pins,
 * enabling statments like GPIO_SET_OUTPUT(ALE) to translate into direct DDRx |= (1 << y).
 * Signal which are active low are marked with a '_N' suffix.
 * Some pins are not remappable and are guaranteed to be on that pin.
 * 
 * Information about proprocessor black magic at https://gcc.gnu.org/onlinedocs/cpp/Argument-Prescan.html.
 */

#include <avr/io.h>

#define XXDDR(X)                (DDR##X)
#define XDDR(X)                 (XXDDR(X))
#define DDR(X) 	                (XDDR(X##_PORT))
#define XXPORT(X)               (PORT##X)
#define XPORT(X)                (XXPORT(X))
#define PORT(X)                 (XPORT(X##_PORT))
#define XXPIN(X)                (PIN##X)
#define XPIN(X)                 (XXPIN(X))
#define PIN(X)                  (XPIN(X##_PORT))
#define BIT(X) 	                (X##_BIT)

/**
 * @brief Sets a signal as output.
 * @param X Signal name.
 */
#define GPIO_SET_OUTPUT(X)	    (DDR(X) 	|=  (1 << BIT(X)))
/**
 * @brief Sets a signal as input.
 * @param X Signal name.
 */
#define GPIO_SET_INPUT(X)	    (DDR(X) 	&= ~(1 << BIT(X)))
/**
 * @brief Sets a signal to output high. If signal is input, it will enable pull-up.
 * @param X Signal name.
 */
#define GPIO_OUTPUT_HIGH(X)		(PORT(X) |=  (1 << BIT(X)))
/**
 * @brief Sets a signal to output low. If signal pin is input, it will disable pull-up.
 * @param X Signal name.
 */
#define GPIO_OUTPUT_LOW(X)		(PORT(X) &= ~(1 << BIT(X)))
/**
 * @brief Reads a signal pin.
 * @param X Signal name.
 * @returns Signal logic level.
 */
#define GPIO_GET_INPUT(X)	    ((PIN(X) &   (1 << BIT(X))))

//////////////////////////////////////////////////
///////////       Signal names:       ////////////
//////////////////////////////////////////////////

// Defined here so that autocomplete will work for them.

#define UART_RX                 UART_RX
#define UART_TX                 UART_TX
#define ALE					    ALE
#define RD_N				    RD_N
#define WR_N				    WR_N
#define CLK					    CLK
#define RESET				    RESET
#define HOLD				    HOLD
#define HLDA				    HLDA
#define TEST_N				    TEST_N
#define READY				    READY
#define NMI					    NMI
#define INTR				    INTR
#define INTA_N				    INTA_N
#define SPI_MOSI			    SPI_MOSI
#define SPI_MISO			    SPI_MISO
#define SPI_SCK				    SPI_SCK
#define REG_OE_N			    REG_OE_N
#define RCLK_SH_LD_N            RCLK_SH_LD_N


//////////////////////////////////////////////////
///////       Signal to pin mapping:       ///////
//////////////////////////////////////////////////

// signals which use pin specific features (like pin interrupt, UART, SPI...):

// SPI:
#define SPI_MOSI_PORT		    B
#define SPI_MOSI_BIT		    3
#define SPI_MISO_PORT		    B
#define SPI_MISO_BIT		    4
#define SPI_SCK_PORT		    B
#define SPI_SCK_BIT			    5

// UART:
#define UART_RX_PORT		    D
#define UART_RX_BIT			    0
#define UART_TX_PORT		    D
#define UART_TX_BIT			    1

// Interrupt 0:
#define MCU_CS_PORT			    D
#define MCU_CS_BIT			    2

// Interrupt 1:
#define ALE_PORT			    D
#define ALE_BIT				    3

// Timer-0 OC0B:
#define CLK_PORT			    D
#define CLK_BIT				    5


// generic signals - can be remapped if neccessary:

#define BHE_IN_ADDRESS          (((uint32_t)1) << 20)
#define M_IO_IN_ADDRESS         (((uint32_t)1) << 22)

#define RCLK_SH_LD_N_PORT	    B
#define RCLK_SH_LD_N_BIT	    0
#define TEST_N_PORT			    B
#define TEST_N_BIT			    1
#define INTA_N_PORT			    B
#define INTA_N_BIT			    2

#define HOLD_PORT			    C
#define HOLD_BIT			    0
#define INTR_PORT			    C
#define INTR_BIT			    1
#define RD_N_PORT 			    C
#define RD_N_BIT			    2
#define NMI_PORT			    C
#define NMI_BIT				    3
#define HLDA_PORT			    C
#define HLDA_BIT			    4
#define WR_N_PORT			    C
#define WR_N_BIT			    5

#define RESET_PORT			    D
#define RESET_BIT			    4
#define REG_OE_N_PORT		    D
#define REG_OE_N_BIT		    6
#define READY_PORT			    D
#define READY_BIT			    7

#endif /* GPIO_H_ */
